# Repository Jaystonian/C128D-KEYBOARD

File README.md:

# C128D-KEYBOARD

Mechanical C128D Keyboard replacement using CherryMX keys

2020-10-08:
 * Gerber files of keyboard PCB uploaded 
  (control board gerbers and all KIKAD files will follow shortly)
 
 * STL 3D printables uploaded

2025-02-16:
 * Updated all gerber files.
 * Fixed the capslock problem
 * All keys function correctly to date

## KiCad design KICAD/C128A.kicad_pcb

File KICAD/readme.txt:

V1.04:
 * Sorry if I've left things a bit messy, as I had used one 
schematic file to support two pcb files.
 * LEDs were quite dim, 220R resistors are better suited.

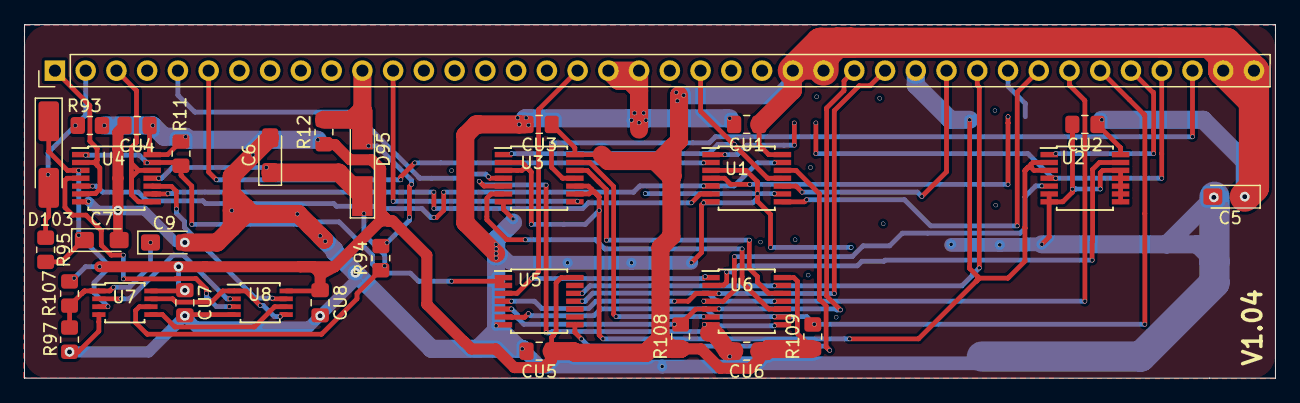
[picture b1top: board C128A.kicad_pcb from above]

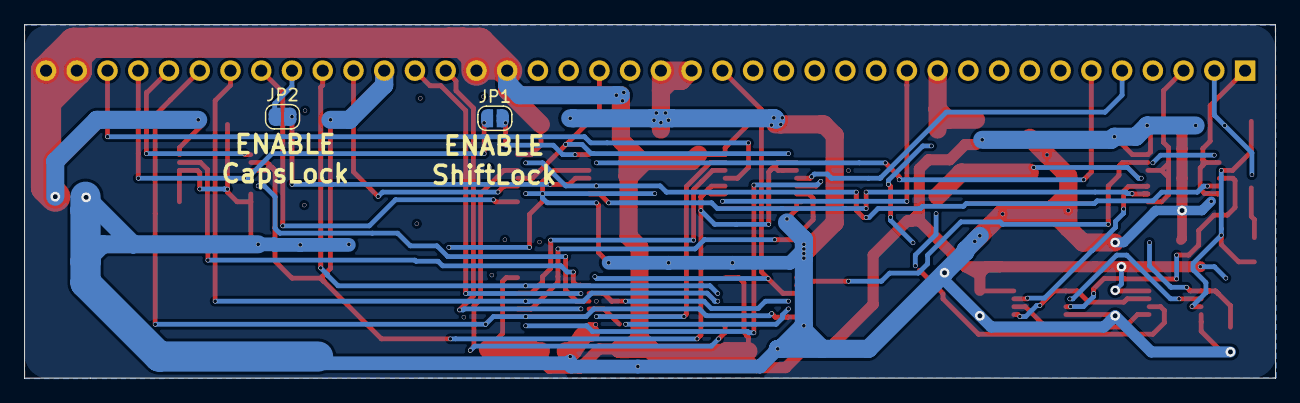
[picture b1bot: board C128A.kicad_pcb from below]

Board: 2 copper layers, 103.4 x 29.2 mm, 34 parts (2 on the bottom side), 43 nets.

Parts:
C5: 10uF; CP_EIA-3216-10_Kemet-I_Pad1.58x1.35mm_HandSolder
C6, C7, C9: 10u; CP_EIA-3216-10_Kemet-I_Pad1.58x1.35mm_HandSolder
CU1, CU2, CU3, CU4, CU5, CU6, CU7, CU8: 100nF; C_0805_2012Metric_Pad1.18x1.45mm_HandSolder
D95, D103: D_MiniMELF_Handsoldering
J2: Conn_01x40; PinHeader_1x40_P2.54mm_Vertical
JP1, JP2: SolderJumper_2_Open; SolderJumper-2_P1.3mm_Open_RoundedPad1.0x1.5mm
R11: 22K; R_0805_2012Metric_Pad1.20x1.40mm_HandSolder
R12, R93: 10K; R_0805_2012Metric_Pad1.20x1.40mm_HandSolder
R94, R95, R107: 2K7; R_0805_2012Metric_Pad1.20x1.40mm_HandSolder
R97: 5K6; R_0805_2012Metric_Pad1.20x1.40mm_HandSolder
R108, R109: 47K; R_0805_2012Metric_Pad1.20x1.40mm_HandSolder
U1, U2, U3: 74HCT4066PW,118; TSSOP-14_4.4x5mm_P0.65mm
U4: 74HCT74PW,118; TSSOP-14_4.4x5mm_P0.65mm
U5: 74HCT30PW,118; TSSOP-14_4.4x5mm_P0.65mm
U6: 74HCT04PW,118; TSSOP-14_4.4x5mm_P0.65mm
U7: 74HCT3G04DP,125; TSSOP-8_3x3mm_P0.65mm
U8: 74HCT2G00DP,125; TSSOP-8_3x3mm_P0.65mm

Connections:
+5V: C5.1, CU1.1, CU2.1, CU3.1, CU4.1, CU5.1, CU6.1, CU7.1, CU8.1, J2.25, J2.26, J2.39, J2.40, R11.1, R12.1, R93.1, R107.1, R108.1, R109.1, U1.14 (VDD), U2.14 (VDD), U3.14 (VDD), U4.14 (VCC), U5.14 (VCC), U6.14 (VCC), U7.8 (VCC), U8.8 (VCC)
/DCL: D103.2 (A), J2.2, R93.2, R95.2
/P05: J2.38, U3.11
/P06: J2.12, U3.8
/P07: J2.5, U3.4
/P08: J2.22, U1.11, U3.1
/P09: J2.37, JP1.1 (A), U2.4
/P10: J2.36, U2.1
/P13: J2.29, U2.2, U2.3, U3.2, U3.3, U3.9, U3.10
/P14: J2.30, U1.10
/P19: J2.6, U1.2
/P24: J2.33, U1.8
/P25: J2.32, JP2.1 (A)
/P4080: D95.2 (A), J2.11, R12.2, R94.2
/PULLUP: R11.2, U4.1 (~R), U4.13 (~R), U5.1, U5.2
/~PushCL: J2.18, U5.3, U6.1
/~PushCU: J2.28, U5.4, U6.3
/~PushF2: J2.27, R108.2, U5.5, U6.5
/~PushF4: J2.35, R109.2, U5.6, U6.9
/~PushF6: J2.34, U5.11, U6.11
/~PushF8: J2.31, U5.12, U6.13
/~Q4080: J2.3, U4.8 (~Q), U4.12 (D)
/~QCL: J2.1, U4.2 (D), U4.6 (~Q)
/~SRS: U7.7, U8.1, U8.5
GND: C5.2, C6.2, C7.2, C9.2, CU1.2, CU2.2, CU3.2, CU4.2, CU5.2, CU6.2, CU7.2, CU8.2, J2.19, J2.20, R97.2, U1.3, U1.7 (VSS), U1.9, U2.6, U2.7 (VSS), U2.8, U2.9, U2.10, U2.11, U2.12, U3.7 (VSS), U4.7 (GND), U5.7 (GND), U6.7 (GND), U7.4 (GND), U8.4 (GND)
unnamed: C9.1, R97.1, R107.2, U7.1
unnamed: C6.1, D95.1 (K), R94.1, U4.11 (C), U7.6
unnamed: C7.1, D103.1 (K), R95.1, U4.3 (C), U7.3
unnamed: JP1.2 (B), U1.1
unnamed: JP2.2 (B), U1.4
unnamed: U1.12, U5.8
unnamed: U2.5, U6.4
unnamed: U2.13, U6.2
unnamed: U3.5, U6.8
unnamed: U3.6, U6.10
unnamed: U3.12, U6.12
unnamed: U3.13, U6.6
unnamed: U1.5, U1.13, U4.5 (Q)
unnamed: U4.4 (~S), U8.3
unnamed: U1.6, U4.9 (Q)
unnamed: U4.10 (~S), U8.7
unnamed: U7.2, U8.2
unnamed: U7.5, U8.6

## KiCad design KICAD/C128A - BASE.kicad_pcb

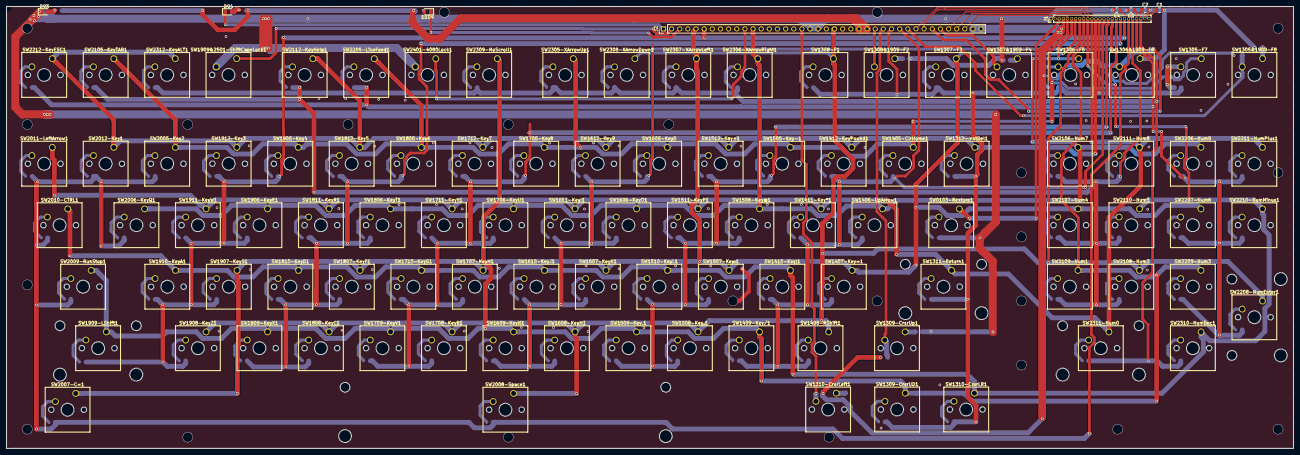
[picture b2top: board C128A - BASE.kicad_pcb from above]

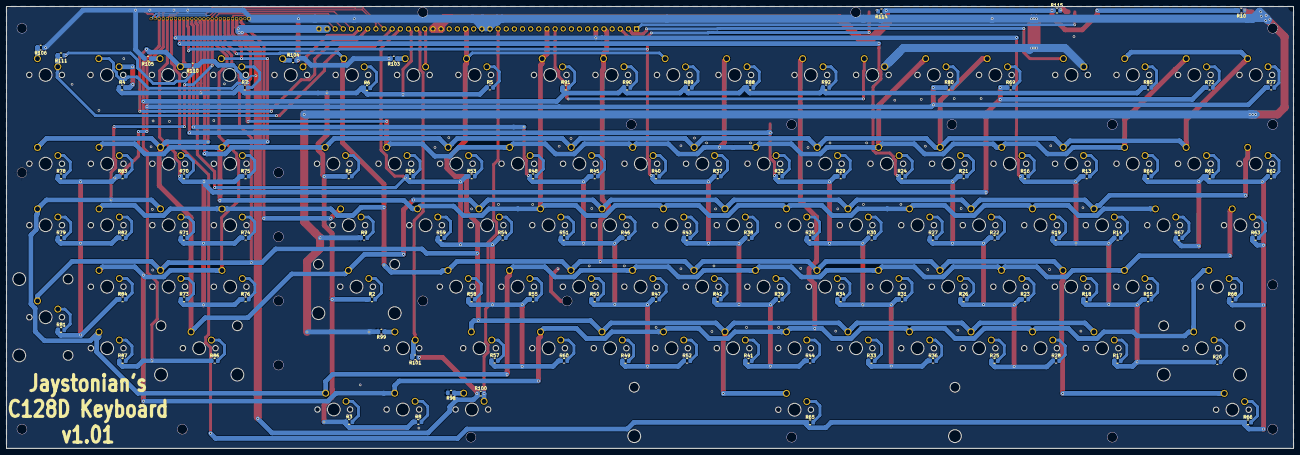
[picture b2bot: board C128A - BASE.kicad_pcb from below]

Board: 2 copper layers, 401.3 x 137.8 mm, 208 parts (102 on the bottom side), 132 nets.

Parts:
C1, C2, C3, C4: 220pF; C_0805_2012Metric_Pad1.18x1.45mm_HandSolder
D93: LED_POWER; LED_0805_2012Metric_Pad1.15x1.40mm_HandSolder
D94: LED_Caps; LED_0805_2012Metric_Pad1.15x1.40mm_HandSolder
D104: LED_4080; LED_0805_2012Metric_Pad1.15x1.40mm_HandSolder
J1: Conn_01x25; PinHeader_1x25_P1.27mm_Vertical
J2: Conn_01x40; PinHeader_1x40_P2.54mm_Vertical
R1, R2, R3, R4, R5, R6, R7, R8, R9, R13, R14, R15, R16, R17, R18, R19, R20, R21, R22, R23, R24, R25, R26, R27, R28, R29, R30, R31, R32, R33, R34, R35, R36, R37, R38, R39, R40, R41, R42, R43, R44, R45, R46, R47, R48, R49, R50, R51, R52, R53, R54, R55, R56, R57, R58, R59, R60, R61, R62, R63, R64, R65, R66, R67, R68, R69, R70, R71, R72, R73, R74, R75, R76, R77, R78, R79, R80, R81, R82, R83, R84, R85, R86, R87, R88, R89, R90, R91, R92: 120R; R_0805_2012Metric_Pad1.20x1.40mm_HandSolder
R10, R114, R115: 1k5; R_0805_2012Metric_Pad1.20x1.40mm_HandSolder
R98, R99, R103, R105, R106: 10K; R_0805_2012Metric_Pad1.20x1.40mm_HandSolder
R100, R101, R110, R111: 47K; R_0805_2012Metric_Pad1.20x1.40mm_HandSolder
R104: 10k; R_0805_2012Metric_Pad1.20x1.40mm_HandSolder
SW0103-Restore1, SW2010-CTRL1: SW_Push; SW_Cherry_MX_1.50u_PCB
SW1305&1909-F8, SW1305-F7, SW1306&1909-F6, SW1306-F5, SW1307&1909-F4, SW1307-F3, SW1308&1909-F2, SW1308-F1, SW1310-CrsrLR1, SW1310-CrsrLeft1, SW1312-InstDel1, SW1405-ClrHome1, SW1406-UpArrow1, SW1407-Key=1, SW1409-Key/1, SW1410-Key;1, SW1411-Key*1, SW1412-KeyPound1, SW1505-Key-1, SW1506-Key@1, SW1507-Key:1, SW1508-Key.1, SW1509-Key,1, SW1510-KeyL1, SW1511-KeyP1, SW1512-Key+1, SW1605-Key0, SW1606-KeyO1, SW1607-KeyK1, SW1608-KeyM1, SW1609-KeyN1, SW1610-KeyJ1, SW1611-KeyI1, SW1612-Key9, SW1705-Key8, SW1706-KeyU1, SW1707-KeyH1, SW1708-KeyB1, SW1709-KeyV1, SW1710-KeyG1, SW1711-KeyY1, SW1712-Key7, SW1805-Key6, SW1806-KeyT1, SW1807-KeyF1, SW1808-KeyC1, SW1809-KeyX1, SW1810-KeyD1, SW1811-KeyR1, SW1812-Key5, SW1905-Key4, SW1906-KeyE1, SW1907-KeyS1, SW1908-KeyZ1, SW1909&2501-ShiftCapsLock1, SW1910-KeyA1, SW1911-KeyW1, SW1912-Key3, SW2005-Key2, SW2006-KeyQ1, SW2011-LeftArrow1, SW2012-Key1, SW2105-KeyTAB1, SW2106-Num7, SW2107-Num4, SW2108-Num2, SW2109-Num1, SW2110-Num5, SW2111-Num8, SW2112-KeyHelp1, SW2205-LineFeed1, SW2206-Num9, SW2207-Num6, SW2209-Num3, SW2210-NumMinus1, SW2211-NumPlus1, SW2212-KeyESC1, SW2305-XArrowUp1, SW2306-XArrowRight1, SW2307-XArrowLeft1, SW2308-XArrowDown1, SW2309-NoScroll1, SW2310-NumDec1, SW2312-KeyALT1, SW2401-4080Lock1: SW_Push; SW_Cherry_MX_1.00u_PCB
SW1309-CrsrUD1, SW1309-CrsrUp1, SW1408-RShift1, SW2007-C=1: SW_Push; SW_Cherry_MX_1.25u_PCB
SW1311-Return1, SW1909-LShift1: SW_Push; SW_Cherry_MX_2.25u_PCB
SW2008-Space1: SW_Push; SW_Cherry_MX_6.25u_PCB
SW2009-RunStop1: SW_Push; SW_Cherry_MX_1.75u_PCB
SW2208-NumEnter1: SW_Push; SW_Cherry_MX_2.00u_Vertical_PCB
SW2311-Num0: SW_Push; SW_Cherry_MX_2.00u_PCB

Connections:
+5V: J1.4, J2.25, J2.26, J2.39, J2.40, R10.2, R100.1, R101.1, R110.1, R111.1, R114.1, R115.1
/DCL: J2.2, SW1909&2501-ShiftCapsLock1.1
/P03: J1.3, SW0103-Restore1.1
/P05: J1.5, J2.38, SW1305-F7.1, SW1405-ClrHome1.1, SW1505-Key-1.1, SW1605-Key0.1, SW1705-Key8.1, SW1805-Key6.1, SW1905-Key4.1, SW2005-Key2.1, SW2105-KeyTAB1.1, SW2205-LineFeed1.1, SW2305-XArrowUp1.1
/P06: J1.6, J2.12, SW1306-F5.1, SW1406-UpArrow1.1, SW1506-Key@1.1, SW1606-KeyO1.1, SW1706-KeyU1.1, SW1806-KeyT1.1, SW1906-KeyE1.1, SW2006-KeyQ1.1, SW2106-Num7.1, SW2206-Num9.1, SW2306-XArrowRight1.1
/P07: J1.7, J2.5, SW1307-F3.1, SW1407-Key=1.1, SW1507-Key:1.1, SW1607-KeyK1.1, SW1707-KeyH1.1, SW1807-KeyF1.1, SW1907-KeyS1.1, SW2007-C=1.1, SW2107-Num4.1, SW2207-Num6.1, SW2307-XArrowLeft1.1
/P08: J1.8, J2.22, SW1308-F1.1, SW1408-RShift1.1, SW1508-Key.1.1, SW1608-KeyM1.1, SW1708-KeyB1.1, SW1808-KeyC1.1, SW1908-KeyZ1.1, SW2008-Space1.1, SW2108-Num2.1, SW2208-NumEnter1.1, SW2308-XArrowDown1.1
/P09: J1.9, J2.37, SW1309-CrsrUD1.1, SW1409-Key/1.1, SW1509-Key,1.1, SW1609-KeyN1.1, SW1709-KeyV1.1, SW1809-KeyX1.1, SW1909-LShift1.1, SW2009-RunStop1.1, SW2109-Num1.1, SW2209-Num3.1, SW2309-NoScroll1.1
/P10: J1.10, J2.36, SW1310-CrsrLR1.1, SW1410-Key;1.1, SW1510-KeyL1.1, SW1610-KeyJ1.1, SW1710-KeyG1.1, SW1810-KeyD1.1, SW1910-KeyA1.1, SW2010-CTRL1.1, SW2110-Num5.1, SW2210-NumMinus1.1, SW2310-NumDec1.1
/P11: J1.11, SW1311-Return1.1, SW1411-Key*1.1, SW1511-KeyP1.1, SW1611-KeyI1.1, SW1711-KeyY1.1, SW1811-KeyR1.1, SW1911-KeyW1.1, SW2011-LeftArrow1.1, SW2111-Num8.1, SW2211-NumPlus1.1, SW2311-Num0.1
/P12: J1.12, SW1312-InstDel1.1, SW1412-KeyPound1.1, SW1512-Key+1.1, SW1612-Key9.1, SW1712-Key7.1, SW1812-Key5.1, SW1912-Key3.1, SW2012-Key1.1, SW2112-KeyHelp1.1, SW2212-KeyESC1.1, SW2312-KeyALT1.1
/P13: J1.13, J2.29, R1.1, R2.1, R3.1, R4.1, R5.1, R6.1, R7.1, R8.1
/P14: J1.14, J2.30, R53.1, R54.1, R55.1, R56.1, R57.1, R58.1, R59.1, R60.1
/P15: J1.15, R45.1, R46.1, R47.1, R48.1, R49.1, R50.1, R51.1, R52.1
/P16: J1.16, R37.1, R38.1, R39.1, R40.1, R41.1, R42.1, R43.1, R44.1
/P17: J1.17, R29.1, R30.1, R31.1, R32.1, R33.1, R34.1, R35.1, R36.1
/P18: J1.18, R21.1, R22.1, R23.1, R24.1, R25.1, R26.1, R27.1, R28.1
/P19: J1.19, J2.6, R13.1, R14.1, R15.1, R16.1, R17.1, R18.1, R19.1, R20.1
/P20: J1.20, R61.1, R62.1, R63.1, R64.1, R65.1, R66.1, R67.1, R68.1
/P21: C4.1, J1.21, R69.1, R70.1, R71.1, R72.1, R73.1, R74.1, R75.1, R76.1
/P22: C3.1, J1.22, R77.1, R78.1, R79.1, R80.1, R81.1, R82.1, R83.1, R84.1
/P23: C2.1, J1.23, R85.1, R86.1, R87.1, R88.1, R89.1, R90.1, R91.1, R92.1
/P24: C1.1, J1.24, J2.33
/P25: J1.25, J2.32
/P4080: J2.11, SW2401-4080Lock1.1
/~PushCL: J2.18, R100.2, SW1310-CrsrLeft1.2
/~PushCU: J2.28, R101.2, SW1309-CrsrUp1.2
/~PushF2: J2.27, SW1308&1909-F2.2
/~PushF4: J2.35, SW1307&1909-F4.2
/~PushF6: J2.34, R110.2, SW1306&1909-F6.2
/~PushF8: J2.31, R111.2, SW1305&1909-F8.2
/~Q4080: D104.1 (K), J2.3
/~QCL: D94.1 (K), J2.1
GND: C1.2, C2.2, C3.2, C4.2, D93.1 (K), J1.1, J2.19, J2.20, R9.1, R98.2, R99.2, R103.2, R104.2, R105.2, R106.1, SW1909&2501-ShiftCapsLock1.2, SW2401-4080Lock1.2
unnamed: D93.2 (A), R10.1
unnamed: D94.2 (A), R115.2
unnamed: D104.2 (A), R114.2
unnamed: R1.2, SW1312-InstDel1.2
unnamed: R2.2, SW1311-Return1.2
unnamed: R3.2, SW1310-CrsrLR1.2
unnamed: R4.2, SW1305-F7.2
unnamed: R5.2, SW1308-F1.2
unnamed: R6.2, SW1307-F3.2
unnamed: R7.2, SW1306-F5.2
unnamed: R8.2, SW1309-CrsrUD1.2
unnamed: R9.2, SW0103-Restore1.2
unnamed: R13.2, SW1912-Key3.2
unnamed: R14.2, SW1911-KeyW1.2
unnamed: R15.2, SW1910-KeyA1.2
unnamed: R16.2, SW1905-Key4.2
unnamed: R17.2, SW1908-KeyZ1.2
unnamed: R18.2, SW1907-KeyS1.2
unnamed: R19.2, SW1906-KeyE1.2
unnamed: R20.2, SW1909-LShift1.2
unnamed: R21.2, SW1812-Key5.2
unnamed: R22.2, SW1811-KeyR1.2
unnamed: R23.2, SW1810-KeyD1.2
unnamed: R24.2, SW1805-Key6.2
unnamed: R25.2, SW1808-KeyC1.2
unnamed: R26.2, SW1807-KeyF1.2
unnamed: R27.2, SW1806-KeyT1.2
unnamed: R28.2, SW1809-KeyX1.2
unnamed: R29.2, SW1712-Key7.2
unnamed: R30.2, SW1711-KeyY1.2
unnamed: R31.2, SW1710-KeyG1.2
unnamed: R32.2, SW1705-Key8.2
unnamed: R33.2, SW1708-KeyB1.2
unnamed: R34.2, SW1707-KeyH1.2
unnamed: R35.2, SW1706-KeyU1.2
unnamed: R36.2, SW1709-KeyV1.2
unnamed: R37.2, SW1612-Key9.2
unnamed: R38.2, SW1611-KeyI1.2
unnamed: R39.2, SW1610-KeyJ1.2
unnamed: R40.2, SW1605-Key0.2
unnamed: R41.2, SW1608-KeyM1.2
unnamed: R42.2, SW1607-KeyK1.2
unnamed: R43.2, SW1606-KeyO1.2
unnamed: R44.2, SW1609-KeyN1.2
unnamed: R45.2, SW1512-Key+1.2
unnamed: R46.2, SW1511-KeyP1.2
unnamed: R47.2, SW1510-KeyL1.2
unnamed: R48.2, SW1505-Key-1.2
unnamed: R49.2, SW1508-Key.1.2
unnamed: R50.2, SW1507-Key:1.2
unnamed: R51.2, SW1506-Key@1.2
unnamed: R52.2, SW1509-Key,1.2
unnamed: R53.2, SW1412-KeyPound1.2
unnamed: R54.2, SW1411-Key*1.2
unnamed: R55.2, SW1410-Key;1.2
unnamed: R56.2, SW1405-ClrHome1.2
unnamed: R57.2, SW1408-RShift1.2
unnamed: R58.2, SW1407-Key=1.2
unnamed: R59.2, SW1406-UpArrow1.2
unnamed: R60.2, SW1409-Key/1.2
unnamed: R61.2, SW2012-Key1.2
unnamed: R62.2, SW2011-LeftArrow1.2
unnamed: R63.2, SW2010-CTRL1.2
unnamed: R64.2, SW2005-Key2.2
unnamed: R65.2, SW2008-Space1.2
unnamed: R66.2, SW2007-C=1.2
unnamed: R67.2, SW2006-KeyQ1.2
unnamed: R68.2, SW2009-RunStop1.2
unnamed: R69.2, SW2112-KeyHelp1.2
unnamed: R70.2, SW2111-Num8.2
unnamed: R71.2, SW2110-Num5.2
unnamed: R72.2, SW2105-KeyTAB1.2
unnamed: R73.2, SW2108-Num2.2
unnamed: R74.2, SW2107-Num4.2
unnamed: R75.2, SW2106-Num7.2
unnamed: R76.2, SW2109-Num1.2
unnamed: R77.2, SW2212-KeyESC1.2
unnamed: R78.2, SW2211-NumPlus1.2
unnamed: R79.2, SW2210-NumMinus1.2
unnamed: R80.2, SW2205-LineFeed1.2
unnamed: R81.2, SW2208-NumEnter1.2
unnamed: R82.2, SW2207-Num6.2
unnamed: R83.2, SW2206-Num9.2
unnamed: R84.2, SW2209-Num3.2
unnamed: R85.2, SW2312-KeyALT1.2
unnamed: R86.2, SW2311-Num0.2
unnamed: R87.2, SW2310-NumDec1.2
unnamed: R88.2, SW2305-XArrowUp1.2
unnamed: R89.2, SW2308-XArrowDown1.2
unnamed: R90.2, SW2307-XArrowLeft1.2
unnamed: R91.2, SW2306-XArrowRight1.2
unnamed: R92.2, SW2309-NoScroll1.2
unnamed: R98.1, SW1310-CrsrLeft1.1
unnamed: R99.1, SW1309-CrsrUp1.1
unnamed: R103.1, SW1308&1909-F2.1
unnamed: R104.1, SW1307&1909-F4.1
unnamed: R105.1, SW1306&1909-F6.1
unnamed: R106.2, SW1305&1909-F8.1
